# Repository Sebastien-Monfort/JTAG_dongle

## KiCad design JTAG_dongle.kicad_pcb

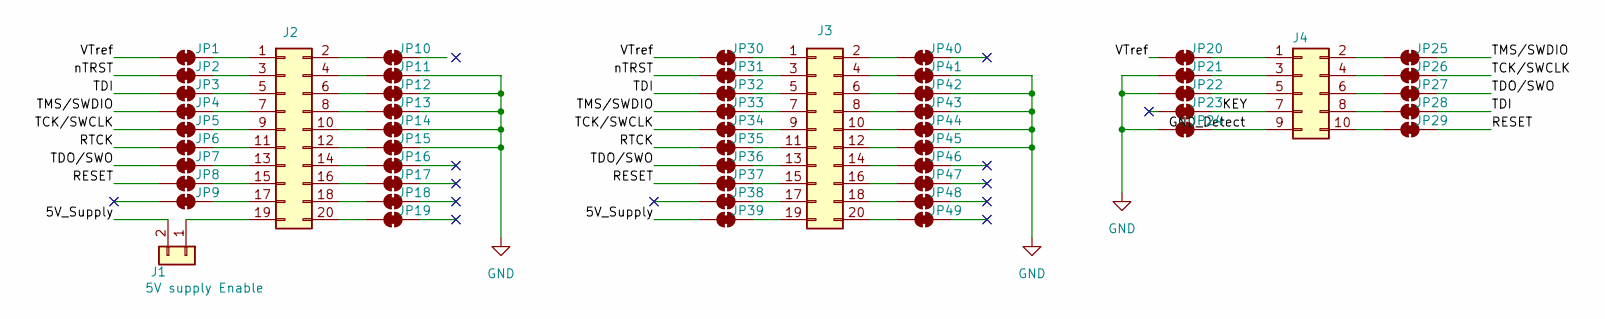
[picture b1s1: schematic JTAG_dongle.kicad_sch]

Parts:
J1: 5V supply Enable; PinHeader_1x02_P2.54mm_Vertical
J2: SeggerJlink connector; SeggerJlinkFemaleConn
J3: Conn_02x10_Odd_Even; PinHeader_2x10_P2.54mm_Vertical
J4: FTS-105-01-F-D; PinHeader_2x05_P1.27mm_Vertical
JP1, JP2, JP3, JP4, JP5, JP6, JP7, JP8, JP9, JP10, JP11, JP12, JP13, JP14, JP15, JP16, JP17, JP18, JP19, JP20, JP21, JP22, JP23, JP24, JP25, JP26, JP27, JP28, JP29, JP30, JP31, JP32, JP33, JP34, JP35, JP36, JP37, JP38, JP39, JP40, JP41, JP42, JP43, JP44, JP45, JP46, JP47, JP48, JP49: SolderJumper_2_Bridged; SolderJumper-2_P1.3mm_Bridged_Pad1.0x1.5mm

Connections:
/5V_Supply: J1.2, JP39.1 (A)
/GND_Detect: J4.9, JP24.2 (B)
/KEY: J4.7, JP23.2 (B)
/RESET: JP8.1 (A), JP29.2 (B), JP37.1 (A)
/RTCK: JP6.1 (A), JP35.1 (A)
/TCK/SWCLK: JP5.1 (A), JP26.2 (B), JP34.1 (A)
/TDI: JP3.1 (A), JP28.2 (B), JP32.1 (A)
/TDO/SWO: JP7.1 (A), JP27.2 (B), JP36.1 (A)
/TMS/SWDIO: JP4.1 (A), JP25.2 (B), JP33.1 (A)
/VTref: JP1.1 (A), JP20.1 (A), JP30.1 (A)
/nTRST: JP2.1 (A), JP31.1 (A)
GND: JP11.2 (B), JP12.2 (B), JP13.2 (B), JP14.2 (B), JP15.2 (B), JP21.1 (A), JP22.1 (A), JP24.1 (A), JP41.2 (B), JP42.2 (B), JP43.2 (B), JP44.2 (B), JP45.2 (B)
unnamed: J1.1, J2.19
unnamed: J2.1, JP1.2 (B)
unnamed: J2.2, JP10.1 (A)
unnamed: J2.3, JP2.2 (B)
unnamed: J2.4, JP11.1 (A)
unnamed: J2.5, JP3.2 (B)
unnamed: J2.6, JP12.1 (A)
unnamed: J2.7, JP4.2 (B)
unnamed: J2.8, JP13.1 (A)
unnamed: J2.9, JP5.2 (B)
unnamed: J2.10, JP14.1 (A)
unnamed: J2.11, JP6.2 (B)
unnamed: J2.12, JP15.1 (A)
unnamed: J2.13, JP7.2 (B)
unnamed: J2.14, JP16.1 (A)
unnamed: J2.15, JP8.2 (B)
unnamed: J2.16, JP17.1 (A)
unnamed: J2.17, JP9.2 (B)
unnamed: J2.18, JP18.1 (A)
unnamed: J2.20, JP19.1 (A)
unnamed: J3.1, JP30.2 (B)
unnamed: J3.2, JP40.1 (A)
unnamed: J3.3, JP31.2 (B)
unnamed: J3.4, JP41.1 (A)
unnamed: J3.5, JP32.2 (B)
unnamed: J3.6, JP42.1 (A)
unnamed: J3.7, JP33.2 (B)
unnamed: J3.8, JP43.1 (A)
unnamed: J3.9, JP34.2 (B)
unnamed: J3.10, JP44.1 (A)
unnamed: J3.11, JP35.2 (B)
unnamed: J3.12, JP45.1 (A)
unnamed: J3.13, JP36.2 (B)
unnamed: J3.14, JP46.1 (A)
unnamed: J3.15, JP37.2 (B)
unnamed: J3.16, JP47.1 (A)
unnamed: J3.17, JP38.2 (B)
unnamed: J3.18, JP48.1 (A)
unnamed: J3.19, JP39.2 (B)
unnamed: J3.20, JP49.1 (A)
unnamed: J4.1, JP20.2 (B)
unnamed: J4.2, JP25.1 (A)
unnamed: J4.3, JP21.2 (B)
unnamed: J4.4, JP26.1 (A)
unnamed: J4.5, JP22.2 (B)
unnamed: J4.6, JP27.1 (A)
unnamed: J4.8, JP28.1 (A)
unnamed: J4.10, JP29.1 (A)

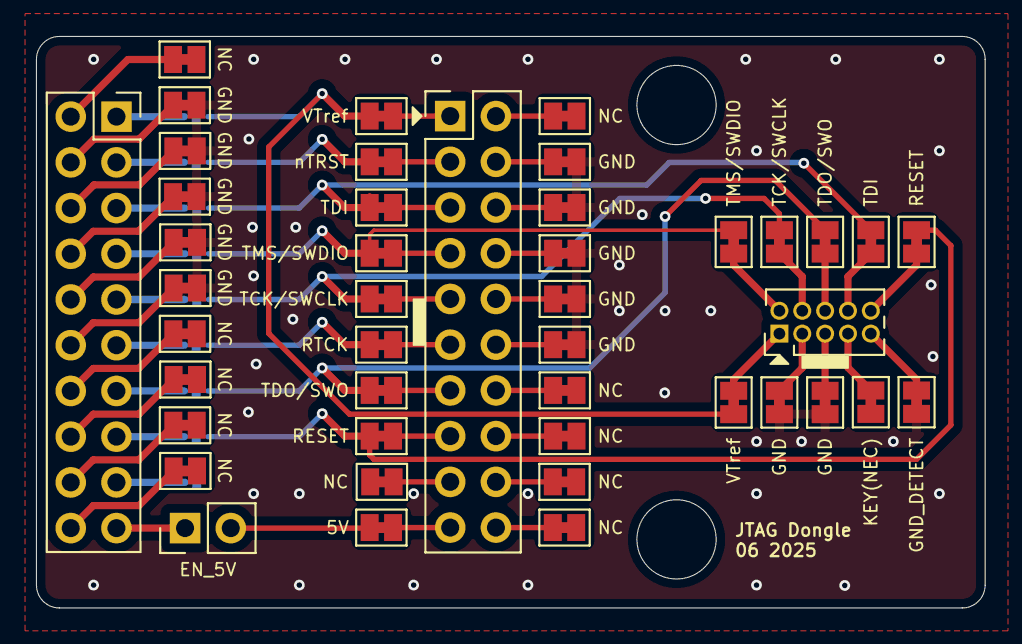
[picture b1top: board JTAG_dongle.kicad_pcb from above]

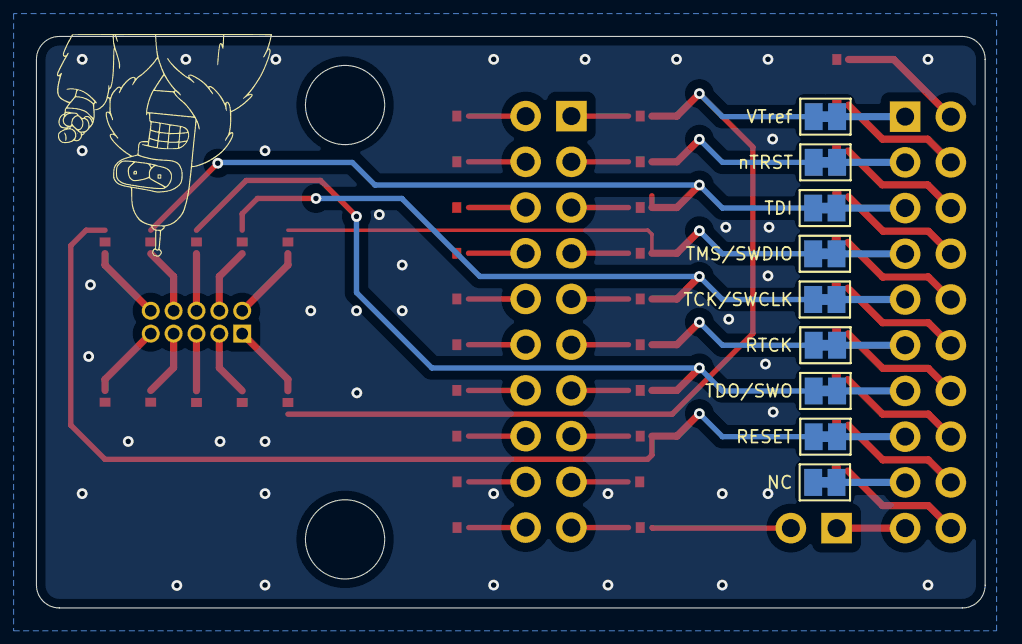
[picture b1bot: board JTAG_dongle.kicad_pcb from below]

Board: 2 copper layers, 52.7 x 31.8 mm, 53 parts (9 on the bottom side), 60 nets.

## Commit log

2025-06-01 first routing
2025-06-01 fix drc erros
2025-06-03 add drawing
